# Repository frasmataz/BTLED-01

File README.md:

# BTLED-01
## Bluetooth-enabled RGB LED driver

An open-hardware PWM driver board for 12V RGB LEDS, specifically 5050 LED strip.

Features an onboard Arduino Nano and HC-05 Bluetooth module for control.

Designed to handle up to 6A current draw, roughly equivalent to 100 5050 LEDs at full brightness on all channels.

Project files are for [Autodesk EAGLE](https://www.autodesk.com/products/eagle/overview).

### Parts list:
 - 1x Arduino Nano
 - 1x HC-05 Bluetooth Module
 - 3x TO-220 N-channel power MOSFETs, rated >2A
 - 1x TO-220 5V linear regulator
 - 2x 0.1µF ceramic capacitor
 - 1x 10µf electrolytic capacitor
 - 3x 100Ω resistor
 - 4x 1kΩ resistor
 - 1x 2.2kΩ resistor
 - 1x 20mm fuse holder & 13A fuse
 - 1x 4-channel 3.5mm pitch screw terminal
 - 1x 5.5x2.5mm DC jack connector

### Board design

### Schematic

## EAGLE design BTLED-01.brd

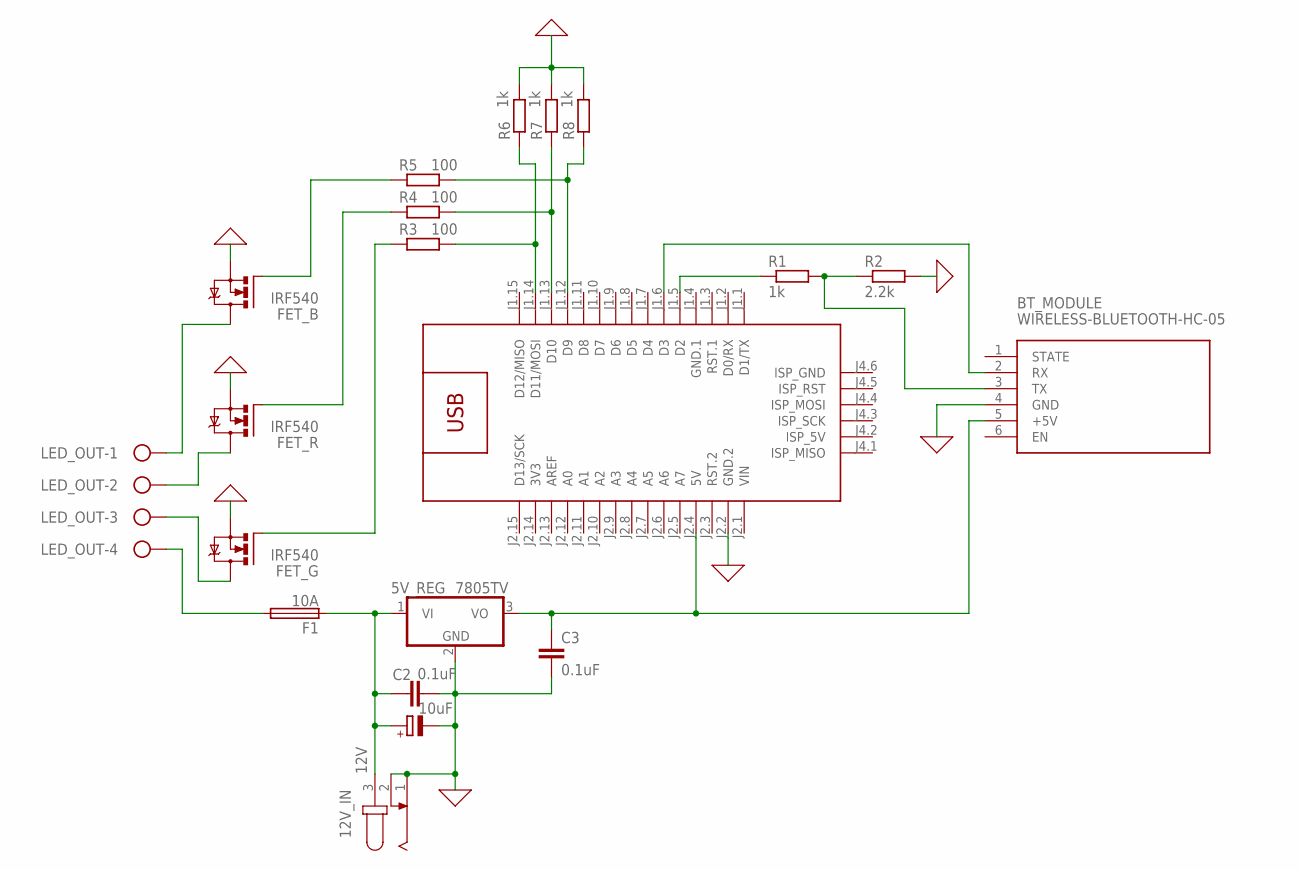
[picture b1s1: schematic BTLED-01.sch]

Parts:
5V_REG: 7805TV; TO220V
12V_IN: 12V; SPC4078
ARDUINO_NANO: ARDUINO-NANO-3.0#ISP
BT_MODULE: WIRELESS-BLUETOOTH-HC-05
C1: 10uF; E2,5-6
C2, C3: 0.1uF; C050-024X044
F1: 10A; SH22,5
FET_B: IRF540; TO220BV
FET_G: IRF540; TO220BV
FET_R: IRF540; TO220BV
LED_OUT: W237-4
R1, R6, R7, R8: 1k; 0204/7
R2: 2.2k; 0204/7
R3, R4, R5: 100; 0204/7

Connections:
3V3: ARDUINO_NANO.J2.14 (3V3)
5V: 5V_REG.3 (VO), ARDUINO_NANO.J2.4 (5V), BT_MODULE.5 (+5V), C3.1
12V_IN: 5V_REG.1 (VI), 12V_IN.3, C1.+, C2.1, F1.1
12V_OUT: F1.2, LED_OUT.4
BT_RX_3.3V: BT_MODULE.3 (TX), R1.2, R2.1
BT_RX_5V: ARDUINO_NANO.J1.5 (D2), R1.1
BT_TX: ARDUINO_NANO.J1.6 (D3), BT_MODULE.2 (RX)
B_DRAIN: FET_B.D, LED_OUT.1
B_SIG_1: ARDUINO_NANO.J1.12 (D9), R5.2, R8.1
B_SIG_2: FET_B.G, R5.1
GND: 5V_REG.2 (GND), 12V_IN.1, 12V_IN.2, ARDUINO_NANO.J2.2 (GND.2), BT_MODULE.4 (GND), C1.-, C2.2, C3.2, FET_B.S, FET_G.S, FET_R.S, R2.2, R6.2, R7.2, R8.2
GND.1: ARDUINO_NANO.J1.4 (GND.1)
G_DRAIN: FET_G.D, LED_OUT.3
G_SIG_1: ARDUINO_NANO.J1.14 (D11/MOSI), R3.2, R6.1
G_SIG_2: FET_G.G, R3.1
R_DRAIN: FET_R.D, LED_OUT.2
R_SIG_1: ARDUINO_NANO.J1.13 (D10), R4.2, R7.1
R_SIG_2: FET_R.G, R4.1
VIN: ARDUINO_NANO.J2.1 (VIN)

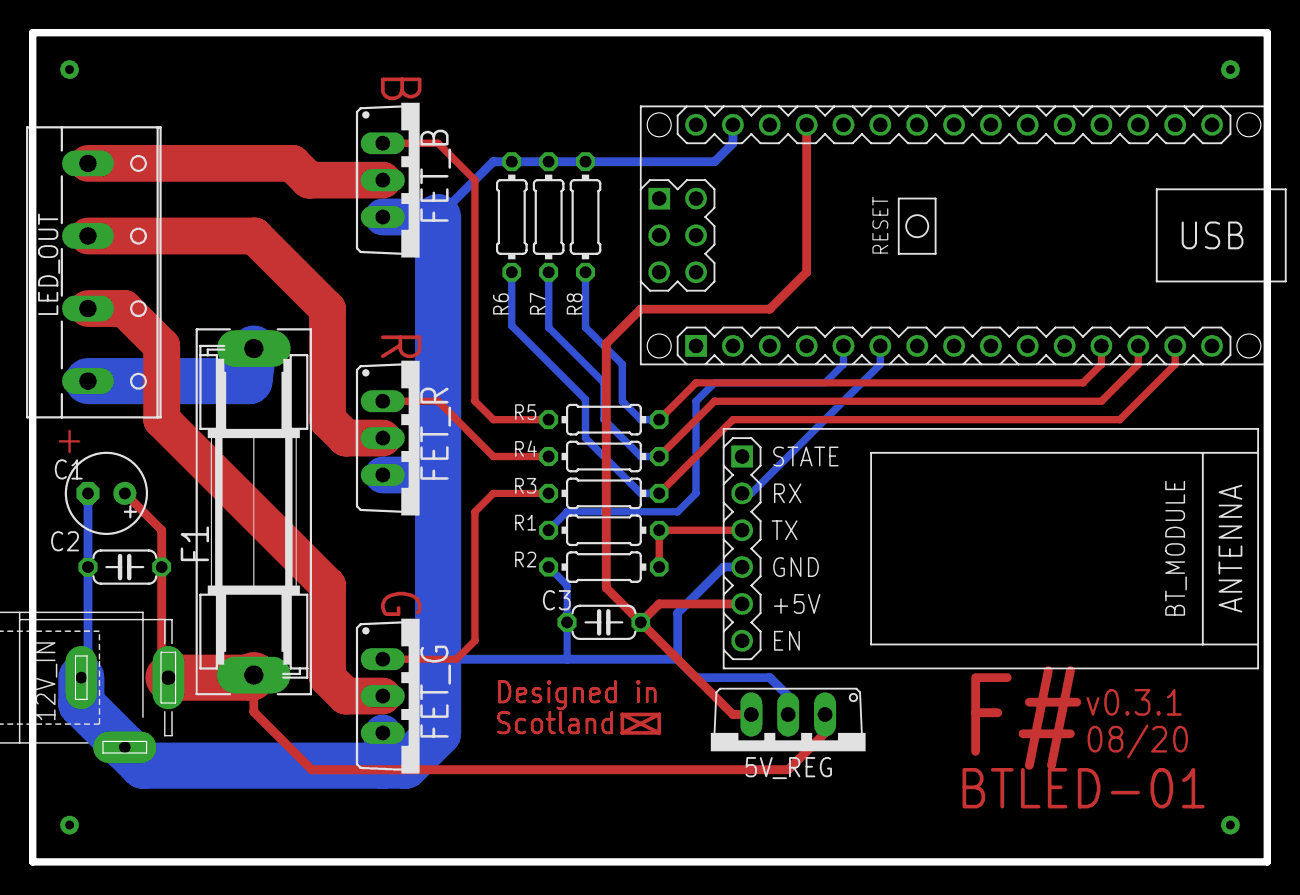
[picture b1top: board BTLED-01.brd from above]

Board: 2 copper layers, 85.1 x 57.2 mm, 20 parts (0 on the bottom side), 16 nets.

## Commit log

2020-07-15 feat: Initial design
2020-07-15 feat: Add README
2020-07-20 fix: Replace fuse holder footprint
    Replace 20mm fuse footprint with 22.5mm fuse holder.
    Tweak some trace widths
2020-07-20 feat: Replaced DC input jack with Wago screw terminals
2020-07-20 feat: Add BRG+ labels to upper copper mask
2020-07-30 fix: tweak fastener holes for easier printing
    also moved some traces a tad
2020-07-31 feat: Add arduino project, set solid LED colours with bluetooth
2020-08-01 feat: Fade List mode now fades with set intervals
2020-08-01 feat: Fade list fading durations now specified in bluetooth command
    This lets you program both the list of colours and the speed of each
    fading animation between each colour remotely.
    Durations are in tenths of a second for now.
    An example bytestream input would be (in hex):
    23 32 FF 00 00 02 07 00 FF 00 0A 00
    23 // start byte
2020-08-04 feat: Add pulldown resistors to MOSFET gate signals
    BREAKING CHANGE: Switched TX/RX pins on Arduino to avoid conflicts with
    built-in serial
2020-08-04 Release 0.3.0
2020-08-05 fix: slight tweaks to positioning
2020-08-05 Release 0.3.1
2021-03-30 feat: add Android project
    also misc tweaks + fixes from prototyping
2021-04-01 feat: Add flicker animation
2021-04-01 feat: Add HSV single colour selection in app

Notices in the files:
parts and their libraries:
diy-modules: Released under the Creative Commons Attribution 4.0 International License: http://creativecommons.org/licenses/by/4.0
